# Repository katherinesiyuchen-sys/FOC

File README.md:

# field-oriented motor controller

A smart servo 79 × 35 mm PCB that mounts behind a gimbal-class brushless motor and turns it into a bus-connected robot joint. 

An STM32G431 runs field-oriented control (FOC) which measures each phase's current through 33 mΩ shunts on the driver's per-phase ground returns
(amplified by the MCU's internal op-amps), reads the rotor angle from an AS5047P 14-bit magnetic encoder over SPI, and drives a DRV8313 three-phase
driver with the PWM pattern that produces exactly the commanded torque. Velocity and position loops sit on top of the current loop, and everything is
commanded over CAN with paired daisy-chain connectors, so several joints share one bus and one power feed.

## Board Layout

## Design notes

**Rev A** -- Jul 22, 2026

Designed from the DRV8313 and STM32G431 datasheets, with ST's B-G431B-ESC1 (UM2516) and mjbots moteus as references for the current-sense
network and CAN servo architecture. Verification was done with `kicad-cli` ERC/DRC plus scripted netlist audits rather than eyeballing. 
Bugs caught before ordering in roughly descending severity:

- MCU VSS pins no-connected (a stray ✕ flag excused all three ground pads)
- The entire GND net silently absorbed into a sense line after a filter cap was deleted during rework
- A UART_TX label dropped onto the reset net, tying PA2 to NRST
- Current-sense networks bypassed on two of three phases
- Thermal vias under the driver's PowerPAD carrying no net. Zones kept clearance from them, which leaves the chip's cooling path open-circuit
- Assorted: swapped charge-pump/LDO bypass caps, a broken VM route, orphan vias, a 3.6 V rail that thought it was 5 V (wrong FB divider)

Every one of these passed visual inspection and most passed ERC.

**Lesson learnt:** Audit the netlist!!!! Not the picture.

## Status

I'm doing this because I want to learn about the mechatronics side of robotics. This will hopefully be developed into a PID project.

**July 23, 2026** 

Rev A ordered from JLCPCB. 4-layer, 79 × 35 mm. Schematic netlist-verified, ERC/DRC clean (0 errors). Awaiting boards;
firmware bring-up starting on ST's B-G431B-ESC1 in the meantime. Bring-up log to follow.

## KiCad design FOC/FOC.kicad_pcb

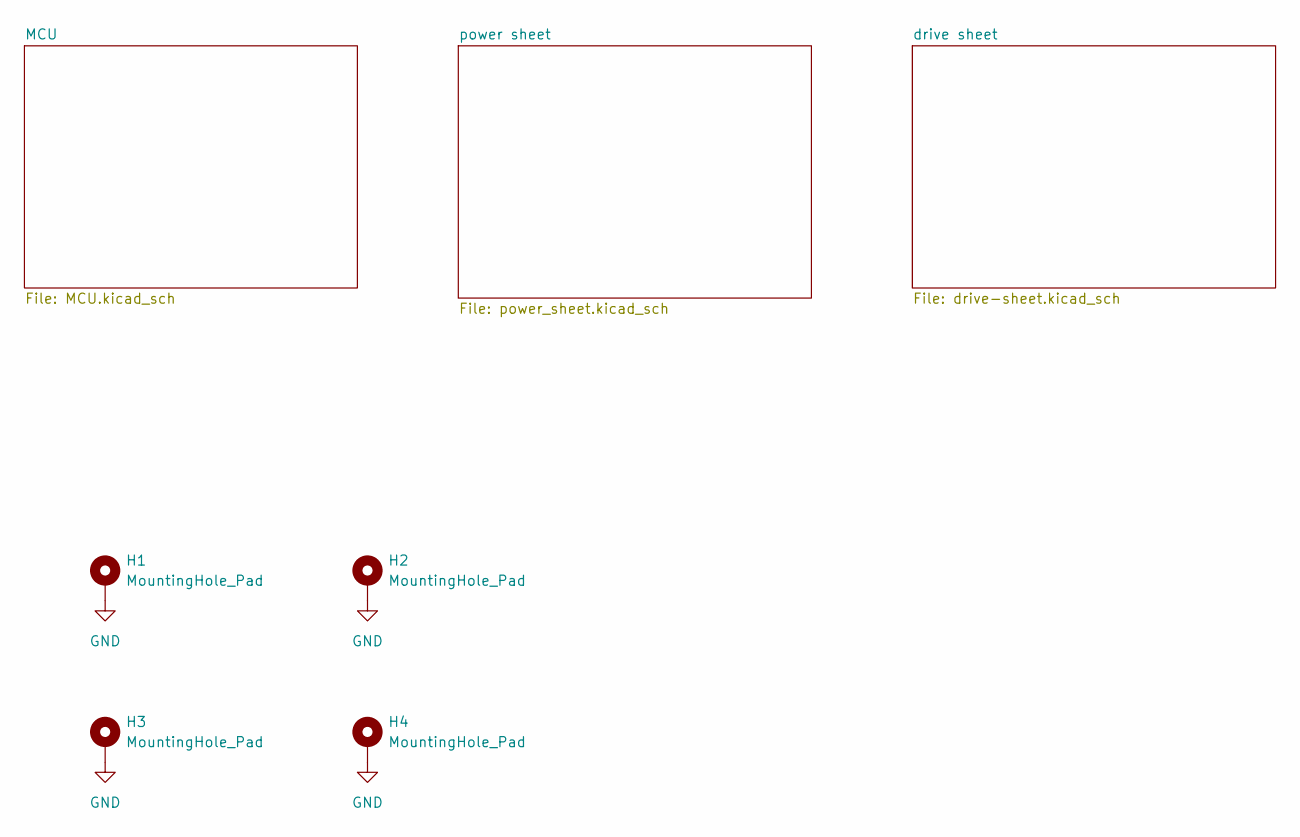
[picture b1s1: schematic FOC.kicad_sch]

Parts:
H1, H2, H3, H4: MountingHole_Pad; MountingHole_2.1mm

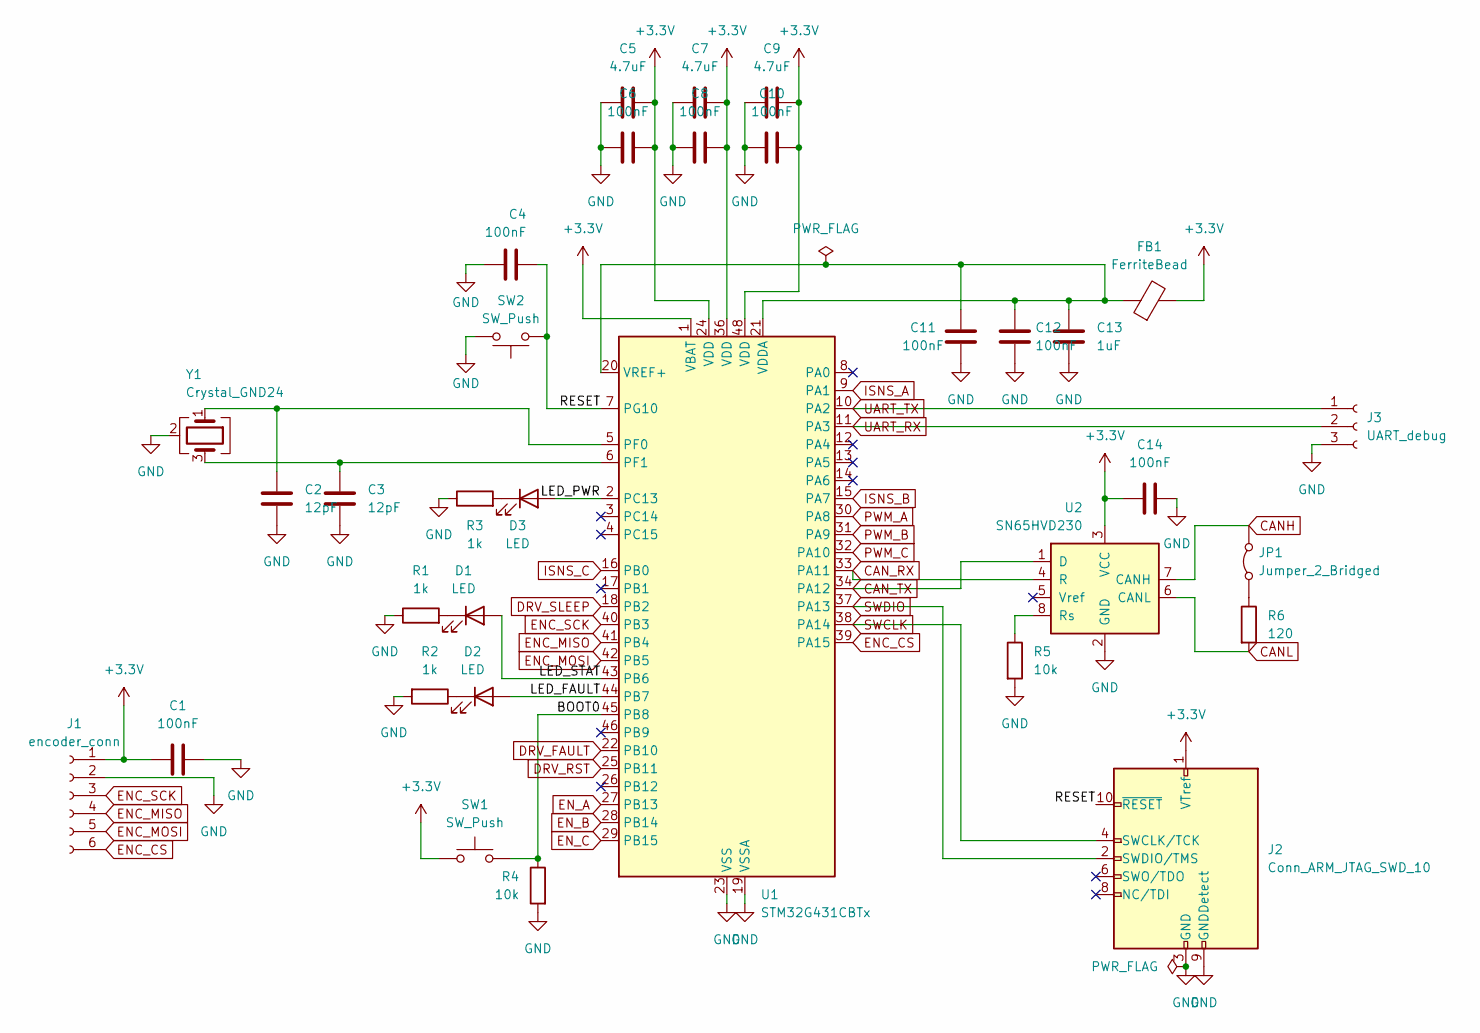
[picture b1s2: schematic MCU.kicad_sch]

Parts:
C1, C4, C6, C8, C10, C11, C12, C14: 100nF; C_0603_1608Metric
C2, C3: 12pF; C_0603_1608Metric
C5, C7, C9: 4.7uF; C_0603_1608Metric
C13: 1uF; C_0603_1608Metric
D1, D2, D3: LED; LED_0603_1608Metric
FB1: FerriteBead; L_0603_1608Metric
J1: encoder_conn; JST_SH_SM06B-SRSS-TB_1x06-1MP_P1.00mm_Horizontal
J2: Conn_ARM_JTAG_SWD_10; PinHeader_2x05_P1.27mm_Vertical_SMD
J3: UART_debug; PinSocket_1x03_P2.54mm_Vertical
JP1: Jumper_2_Bridged; SolderJumper-2_P1.3mm_Bridged_RoundedPad1.0x1.5mm
R1, R2, R3: 1k; R_0603_1608Metric
R4, R5: 10k; R_0603_1608Metric
R6: 120; R_0603_1608Metric
SW1, SW2: SW_Push; SW_SPST_B3S-1000
U1: STM32G431CBTx; LQFP-48_7x7mm_P0.5mm
U2: SN65HVD230; SOIC-8_3.9x4.9mm_P1.27mm
Y1: Crystal_GND24; Crystal_SMD_3225-4Pin_3.2x2.5mm

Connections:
+3.3V: C1.2, C5.2, C6.2, C7.2, C8.2, C9.2, C10.2, C14.1, FB1.2, J1.1, J2.1 (VTref), SW1.1, U1.1 (VBAT), U1.24 (VDD), U1.36 (VDD), U1.48 (VDD), U2.3 (VCC); also elsewhere on the board
/MCU/BOOT0: R4.1, SW1.2, U1.45 (PB8)
/MCU/LED_FAULT: D2.2 (A), U1.44 (PB7)
/MCU/LED_PWR: D3.2 (A), U1.2 (PC13)
/MCU/LED_STAT: D1.2 (A), U1.43 (PB6)
/MCU/RESET: C4.2, J2.10 (~RESET), SW2.1, U1.7 (PG10)
CANH: JP1.2 (B), U2.7 (CANH); also elsewhere on the board
CANL: R6.2, U2.6 (CANL); also elsewhere on the board
CAN_RX: U1.33 (PA11), U2.4 (R)
CAN_TX: U1.34 (PA12), U2.1 (D)
DRV_FAULT: U1.22 (PB10); also elsewhere on the board
DRV_RST: U1.25 (PB11); also elsewhere on the board
DRV_SLEEP: U1.18 (PB2); also elsewhere on the board
ENC_CS: J1.6, U1.39 (PA15)
ENC_MISO: J1.4, U1.41 (PB4)
ENC_MOSI: J1.5, U1.42 (PB5)
ENC_SCK: J1.3, U1.40 (PB3)
EN_A: U1.27 (PB13); also elsewhere on the board
EN_B: U1.28 (PB14); also elsewhere on the board
EN_C: U1.29 (PB15); also elsewhere on the board
GND: C1.1, C2.2, C3.2, C4.1, C5.1, C6.1, C7.1, C8.1, C9.1, C10.1, C11.1, C12.1, C13.2, C14.2, J1.2, J2.3 (GND), J2.5 (GND), J2.9 (GNDDetect), J3.3, R1.1, R2.2, R3.1, R4.2, R5.2, SW2.2, U1.19 (VSSA), U1.23 (VSS), U1.35 (VSS), U1.47 (VSS), U2.2 (GND), Y1.2 (G), Y1.4 (G); also elsewhere on the board
ISNS_A: U1.9 (PA1); also elsewhere on the board
ISNS_B: U1.15 (PA7); also elsewhere on the board
ISNS_C: U1.16 (PB0); also elsewhere on the board
unnamed: D1.1 (K), R1.2
unnamed: D2.1 (K), R2.1
unnamed: D3.1 (K), R3.2
unnamed: JP1.1 (A), R6.1
unnamed: C2.1, U1.5 (PF0), Y1.1
unnamed: C3.1, U1.6 (PF1), Y1.3
unnamed: C11.2, C12.2, C13.1, FB1.1, U1.20 (VREF+), U1.21 (VDDA)
unnamed: R5.1, U2.8 (Rs)
PWM_A: U1.30 (PA8); also elsewhere on the board
PWM_B: U1.31 (PA9); also elsewhere on the board
PWM_C: U1.32 (PA10); also elsewhere on the board
SWCLK: J2.4 (SWCLK/TCK), U1.38 (PA14)
SWDIO: J2.2 (SWDIO/TMS), U1.37 (PA13)
UART_RX: J3.2, U1.11 (PA3)
UART_TX: J3.1, U1.10 (PA2)

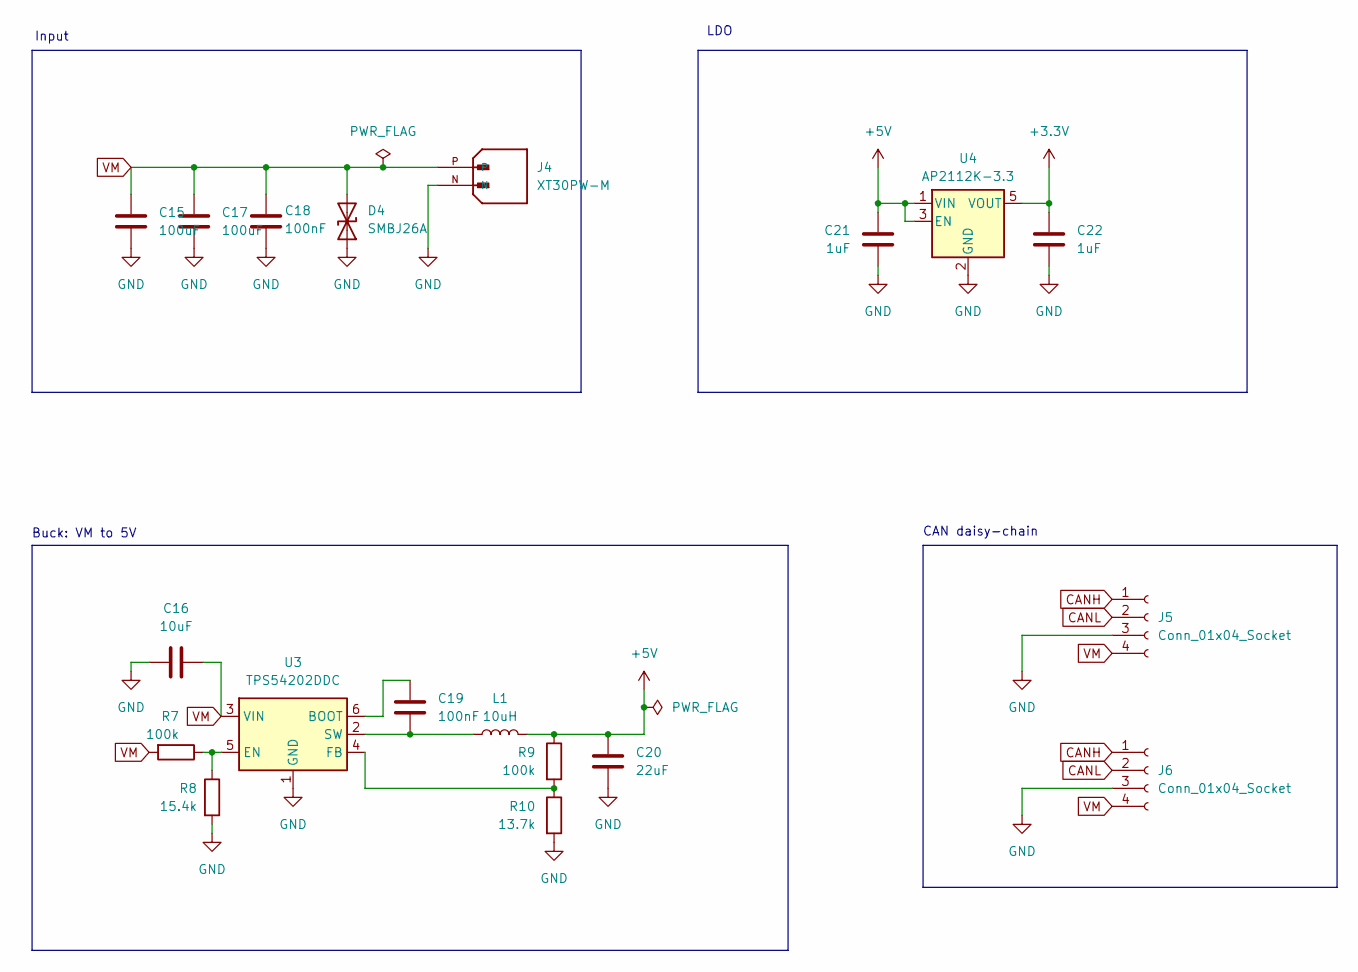
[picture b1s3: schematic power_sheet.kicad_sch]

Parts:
C15, C17: 100uF; CP_Elec_6.3x7.7
C16: 10uF; C_0603_1608Metric
C18, C19: 100nF; C_0603_1608Metric
C20: 22uF; C_0805_2012Metric
C21, C22: 1uF; C_0603_1608Metric
D4: SMBJ26A; D_SMB
J4: XT30PW-M; AMASS_XT30PW-M; PARTREV 1.2
J5, J6: Conn_01x04_Socket; JST_GH_SM04B-GHS-TB_1x04-1MP_P1.25mm_Horizontal
L1: 10uH; L_Taiyo-Yuden_NR-40xx
R7, R9: 100k; R_0603_1608Metric
R8: 15.4k; R_0603_1608Metric
R10: 13.7k; R_0603_1608Metric
U3: TPS54202DDC; SOT-23-6
U4: AP2112K-3.3; SOT-23-5

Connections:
+3.3V: C22.1, U4.5 (VOUT); also elsewhere on the board
+5V: C20.1, C21.1, L1.2, R9.1, U4.1 (VIN), U4.3 (EN)
CANH: J5.1, J6.1; also elsewhere on the board
CANL: J5.2, J6.2; also elsewhere on the board
GND: C15.2, C16.1, C17.2, C18.2, C20.2, C21.2, C22.2, D4.1 (A1), J4.N, J5.3, J6.3, R8.2, R10.2, U3.1 (GND), U4.2 (GND); also elsewhere on the board
unnamed: C19.1, U3.6 (BOOT)
unnamed: R7.1, R8.1, U3.5 (EN)
unnamed: R9.2, R10.1, U3.4 (FB)
unnamed: C19.2, L1.1, U3.2 (SW)
VM: C15.1, C16.2, C17.1, C18.1, D4.2 (A2), J4.P, J5.4, J6.4, R7.2, U3.3 (VIN); also elsewhere on the board

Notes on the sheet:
CAN daisy-chain
Buck: VM to 5V
LDO
Input

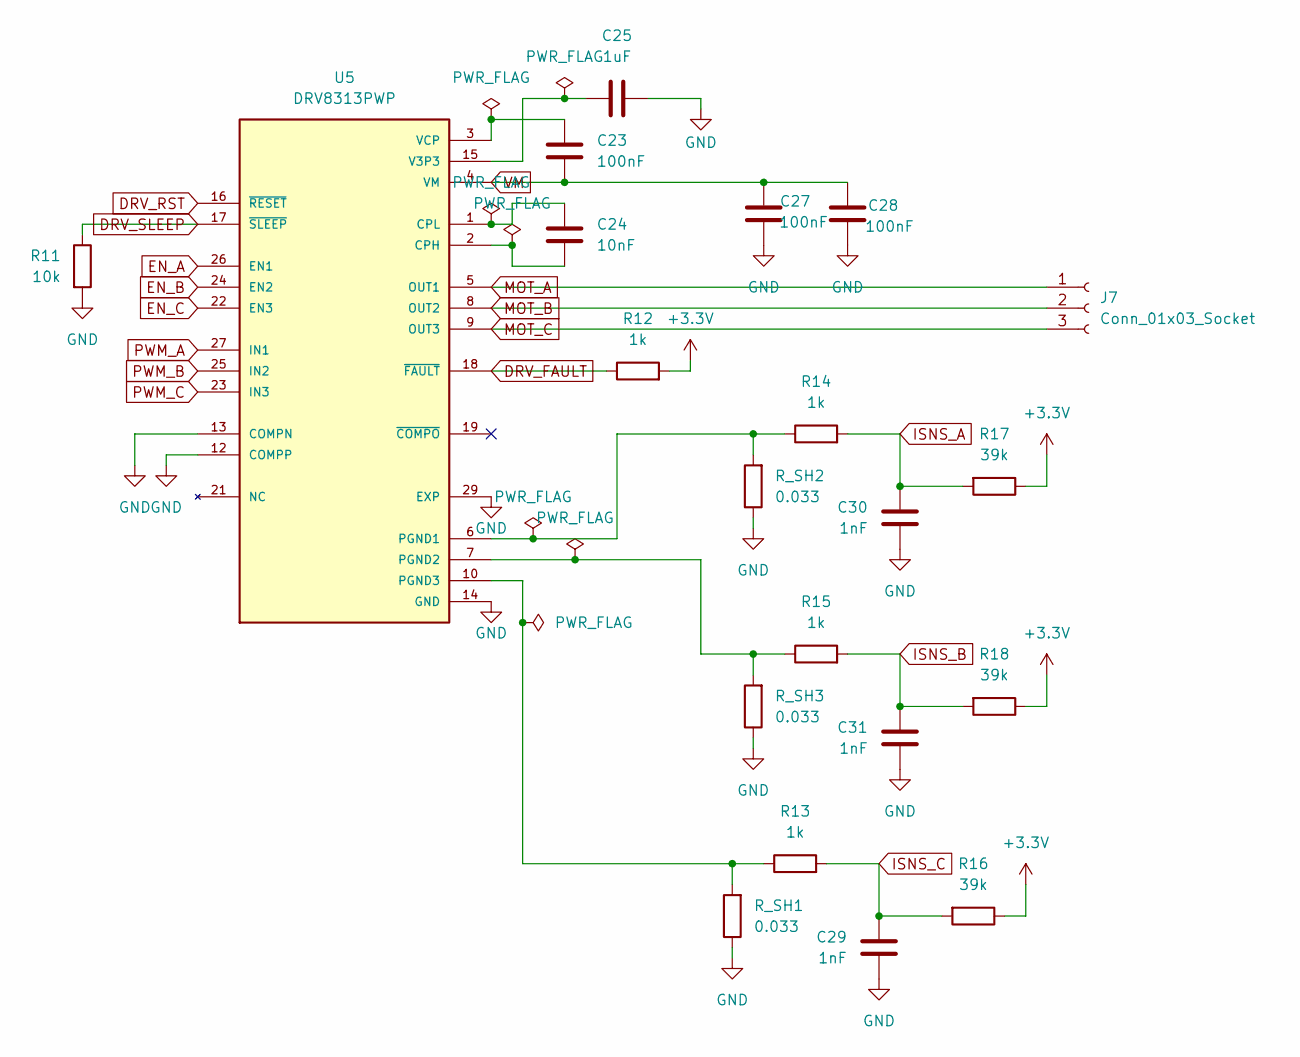
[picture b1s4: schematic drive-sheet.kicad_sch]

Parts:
C23, C27, C28: 100nF; C_0603_1608Metric
C24: 10nF; C_0603_1608Metric
C25: 1uF; C_0603_1608Metric
C29, C30, C31: 1nF; C_0603_1608Metric
J7: Conn_01x03_Socket; TerminalBlock_MetzConnect_Type101_RT01603HBWC_1x03_P5.08mm_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
R11: 10k; R_0603_1608Metric
R12, R13, R14, R15: 1k; R_0603_1608Metric
R16, R17, R18: 39k; R_0603_1608Metric
R_SH1, R_SH2, R_SH3: 0.033; R_2512_6332Metric
U5: DRV8313PWP; SOP65P640X120-29N; PARTREV D

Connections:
+3.3V: R12.2, R16.1, R17.1, R18.1; also elsewhere on the board
DRV_FAULT: R12.1, U5.18 (~FAULT); also elsewhere on the board
DRV_RST: U5.16 (~RESET); also elsewhere on the board
DRV_SLEEP: R11.1, U5.17 (~SLEEP); also elsewhere on the board
EN_A: U5.26 (EN1); also elsewhere on the board
EN_B: U5.24 (EN2); also elsewhere on the board
EN_C: U5.22 (EN3); also elsewhere on the board
GND: C25.2, C27.1, C28.1, C29.2, C30.2, C31.2, R11.2, R_SH1.1, R_SH2.1, R_SH3.1, U5.12 (COMPP), U5.13 (COMPN), U5.14 (GND), U5.20 (GND), U5.28 (GND), U5.29 (EXP); also elsewhere on the board
ISNS_A: C30.1, R14.2, R17.2; also elsewhere on the board
ISNS_B: C31.1, R15.2, R18.2; also elsewhere on the board
ISNS_C: C29.1, R13.2, R16.2; also elsewhere on the board
MOT_A: J7.1, U5.5 (OUT1)
MOT_B: J7.2, U5.8 (OUT2)
MOT_C: J7.3, U5.9 (OUT3)
unnamed: C24.2, U5.2 (CPH)
unnamed: C24.1, U5.1 (CPL)
unnamed: R14.1, R_SH2.2, U5.6 (PGND1)
unnamed: R15.1, R_SH3.2, U5.7 (PGND2)
unnamed: R13.1, R_SH1.2, U5.10 (PGND3)
unnamed: C25.1, U5.15 (V3P3)
unnamed: C23.1, U5.3 (VCP)
PWM_A: U5.27 (IN1); also elsewhere on the board
PWM_B: U5.25 (IN2); also elsewhere on the board
PWM_C: U5.23 (IN3); also elsewhere on the board
VM: C23.2, C27.2, C28.2, U5.4 (VM), U5.11 (VM); also elsewhere on the board

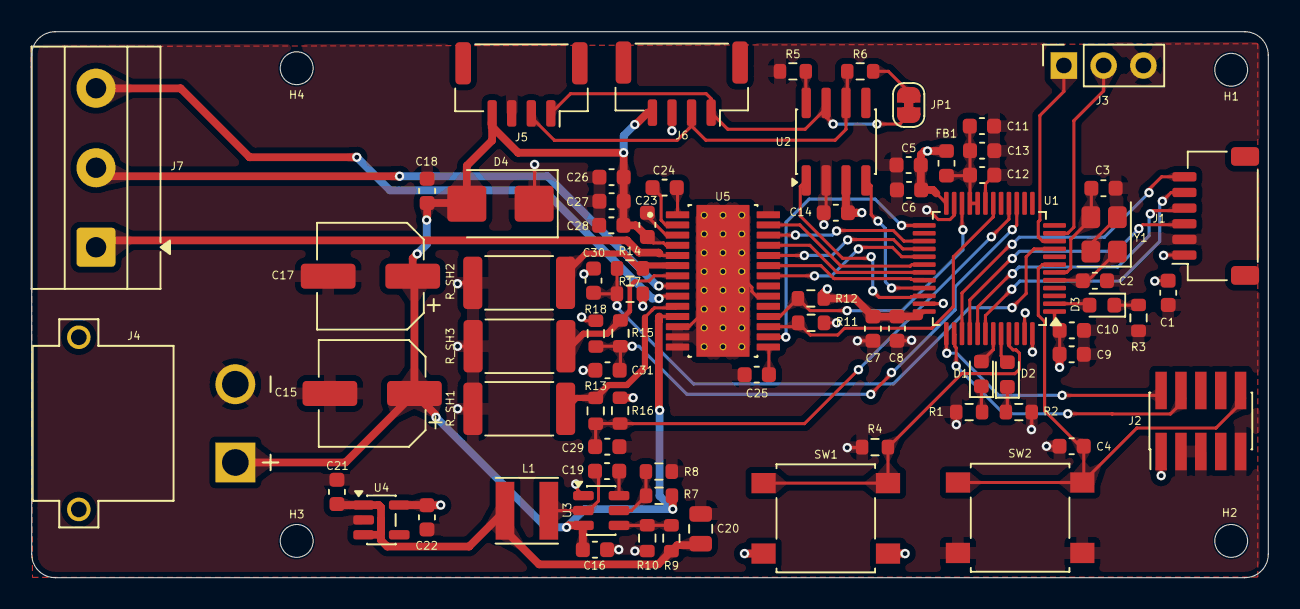
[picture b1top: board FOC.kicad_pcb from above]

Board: 4 copper layers, 79.0 x 34.9 mm, 78 parts (0 on the bottom side), 55 nets.

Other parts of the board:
C26: 10uF; C_0603_1608Metric

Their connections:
GND: C26.1; also elsewhere on the board
VM: C26.2; also elsewhere on the board

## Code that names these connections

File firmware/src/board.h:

// pin map for FOC board

// MCU STM32G431CBT6
// core clock 170 MHz, HSE = 16MHz crystal
#pragma once

// LED: active high
#define LED_PWR_PORT GPIOC
#define LED_PWR_PIN 13
#define LED_STAT_PORT GPIOB
#define LED_STAT_PIN 6
#define LED_FAULT_PORT GPIOB
#define LED_FAULT_PIN 7

// UART debug: USART2, PA2=TX(AF7), PA3=RX(AF7)
#define UART_TX_PIN 2
#define UART_RX_PIN 3

// Encoder AS5047P: 
// SPI1 - PB3 = SCK
// PB4 = MISO
// PB5 = MOSI (AF5)
// PA15 = CS (GPIO)
#define ENC_CS_PORT GPIOA
#define ENC_CS_PIN 15

// DRV8313 control
// PWM: TIM1 CH1/2/3 -> PA8/9/10 (AF6) center-aligned 25kHz
#define PWM_FREQ_HZ 25000
// Enables (per phase, active high): EN_A=PB13, EN_B=PB14, EN_C=PB15
#define EN_A_PIN 13
#define EN_B_PIN 14
#define EN_C_PIN 15
// nSLEEP = PB2 (drive high to wake with 10k pulldown keeps driver off at reset)
#define DRV_SLEEP_PIN 2
// nRESET = PB11 (drive high for run)
#define DRV_RST_PIN 11
// nFAULT = PB10 (input, open-drain, external 10k pullup; low = fault)
#define DRV_FAULT_PIN 10

// Current sense: internal op-amps in PGA x16, low-side shunts 0.033R
// OPAMP1 VINP = PA1 (phase A) --> ADC1
// OPAMP2 VINP = PA7 (phase B) --> ADC2
// OPAMP3 VINP = PA0 (phase C) --> ADC3
#define SHUNT_OHMS 0.033f
#define PGA_GAIN 16.0f
#define VREF_V 3.3f
// amps per ADC count 12-bit: V/count / (gain * Rsh)
#define AMPS_PER_COUNT (VREF_V / 4096.0f / (GPA_GAIN * SHUNT_OHMS))

// CAN: FDCAN1, PA11=RX, PA12=TX (AF9) @ 500 kbit
#define CAN_NODE_ID 0x01

// Motor: iFLight GM4108H-120T
#define MOTOR_POLE_PAIRS 11
#define MOTOR_PHASE_R 11.0f // ohms, placeholder before bringup
#define CURRENT_LIMIT_A 0.5f // bring-up limit
#define VBUS_V 16.0f // placeholder before deciding power supply
